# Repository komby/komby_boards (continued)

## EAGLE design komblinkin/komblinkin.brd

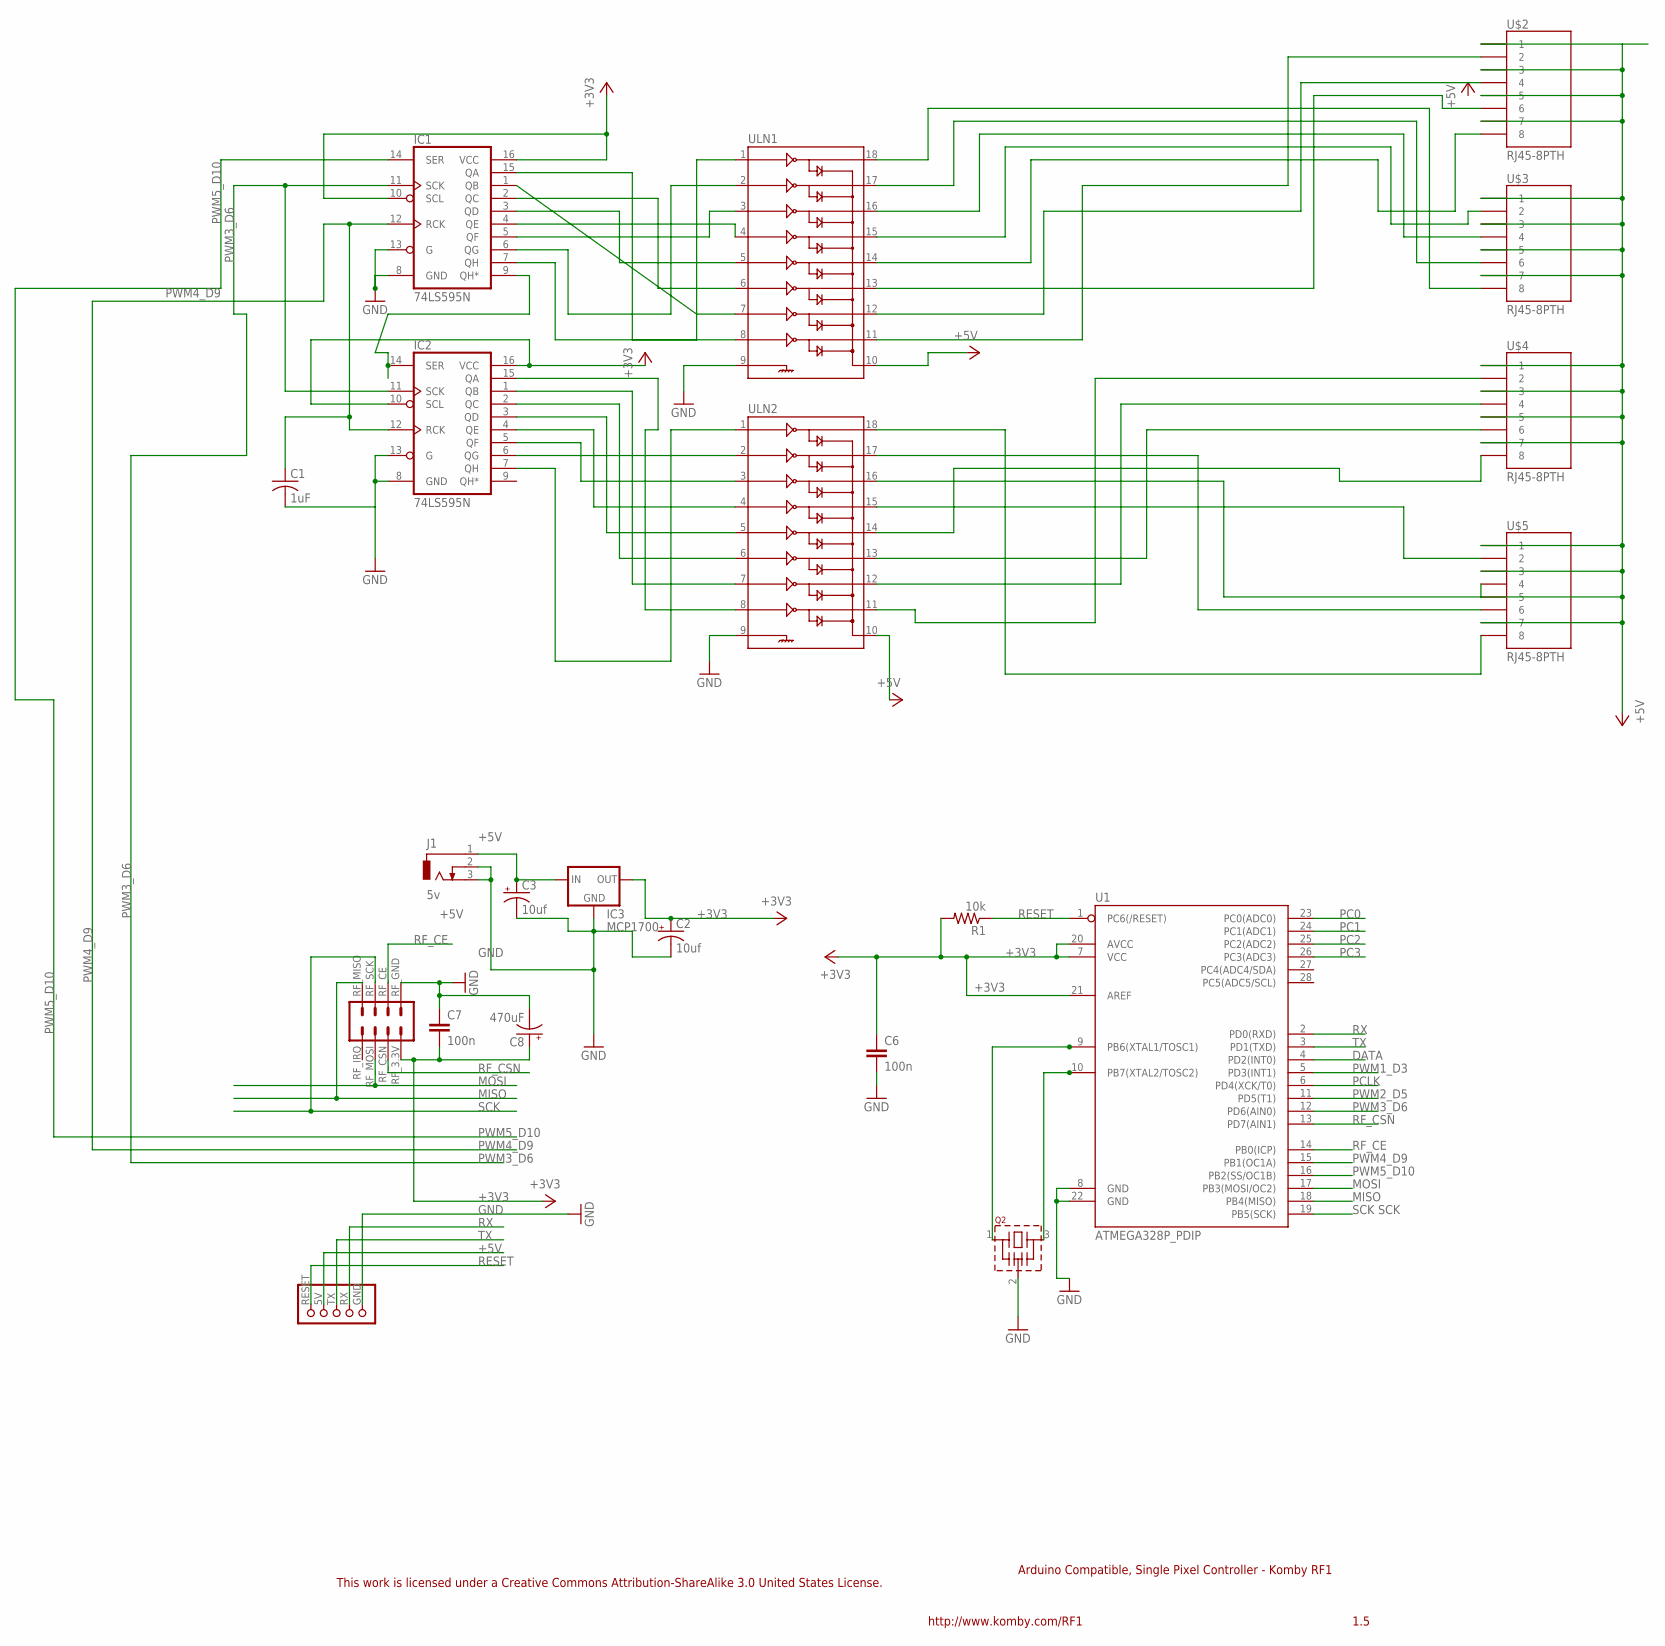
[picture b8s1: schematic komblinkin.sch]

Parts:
C1: 1uF; C050-025X075
C2: 10uf; E1,8-4
C3: 10uf; E5-8,5
C6, C7: 100n; C025-024X044
C8: 470uF; E5-8,5
IC1, IC2: 74LS595N; DIL16
IC3: MCP1700; TO92
J1: 5v; DCJ0303
Q2: CSTLS_X
R1: 10k; 0207/7
U1: ATMEGA328P_PDIP; DIL28-3
U$1: KOMBY_TTL_SERIAL; KOMBY_SERIAL_FOOTPRINT
U$2, U$3, U$4, U$5: RJ45-8PTH; RJ45-8
U$8: NRF24L01_HEADER; NRF24L01
ULN1, ULN2: ULN2803DIP; DIL18

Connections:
+3V3: C2.+, C6.1, C7.2, C8.+, IC1.10 (SCL), IC1.16 (VCC), IC2.10 (SCL), IC2.16 (VCC), IC3.3 (OUT), R1.2, U1.7 (VCC), U1.20 (AVCC), U1.21 (AREF), U$8.RF_3.3V
+5V: C3.+, IC3.2 (IN), J1.1, U$1.5V, U$2.1, U$2.3, U$2.5, U$2.7, U$3.1, U$3.3, U$3.5, U$3.7, U$4.1, U$4.3, U$4.5, U$4.7, U$5.1, U$5.3, U$5.5, U$5.7, ULN1.10, ULN2.10
DATA: U1.4 (PD2(INT0))
GND: C1.2, C2.-, C3.-, C6.2, C7.1, C8.-, IC1.8 (GND), IC1.13 (G), IC2.8 (GND), IC2.13 (G), IC3.1 (GND), J1.2, J1.3, Q2.2 (VSS), U1.8 (GND), U1.22 (GND), U$1.GND, U$8.RF_GND (RFGND_1), ULN1.9, ULN2.9
MISO: U1.18 (PB4(MISO)), U$8.RF_MISO
MOSI: U1.17 (PB3(MOSI/OC2)), U$8.RF_MOSI
unnamed: U$5.8, ULN2.18
unnamed: IC1.15 (QA), ULN1.8
unnamed: IC1.1 (QB), ULN1.7
unnamed: U$3.8, ULN1.18
unnamed: IC1.2 (QC), ULN1.6
unnamed: IC1.3 (QD), ULN1.5
unnamed: IC1.4 (QE), ULN1.4
unnamed: IC1.5 (QF), ULN1.3
unnamed: IC1.9 (QH*), IC2.14 (SER)
unnamed: IC1.6 (QG), ULN1.2
unnamed: U$3.6, ULN1.17
unnamed: IC1.7 (QH), ULN1.1
unnamed: Q2.3, U1.10 (PB7(XTAL2/TOSC2))
unnamed: IC2.1 (QB), ULN2.7
unnamed: IC2.2 (QC), ULN2.6
unnamed: U$3.4, ULN1.16
unnamed: IC2.3 (QD), ULN2.5
unnamed: IC2.4 (QE), ULN2.4
unnamed: IC2.5 (QF), ULN2.3
unnamed: IC2.6 (QG), ULN2.2
unnamed: IC2.7 (QH), ULN2.1
unnamed: U$3.2, ULN1.15
unnamed: U$5.6, ULN2.17
unnamed: U$5.4, ULN2.16
unnamed: U$5.2, ULN2.15
unnamed: U$4.8, ULN2.14
unnamed: U$4.6, ULN2.13
unnamed: U$4.4, ULN2.12
unnamed: U$4.2, ULN2.11
unnamed: IC2.15 (QA), ULN2.8
unnamed: Q2.1, U1.9 (PB6(XTAL1/TOSC1))
unnamed: U$2.8, ULN1.14
unnamed: U$2.6, ULN1.13
unnamed: U$2.4, ULN1.12
unnamed: U$2.2, ULN1.11
PC0: U1.23 (PC0(ADC0))
PC1: U1.24 (PC1(ADC1))
PC2: U1.25 (PC2(ADC2))
PC3: U1.26 (PC3(ADC3))
PCLK: U1.6 (PD4(XCK/T0))
PWM1_D3: U1.5 (PD3(INT1))
PWM2_D5: U1.11 (PD5(T1))
PWM3_D6: IC1.11 (SCK), IC2.11 (SCK), U1.12 (PD6(AIN0))
PWM4_D9: C1.1, IC1.12 (RCK), IC2.12 (RCK), U1.15 (PB1(OC1A))
PWM5_D10: IC1.14 (SER), U1.16 (PB2(SS/OC1B))
RESET: R1.1, U1.1 (PC6(/RESET)), U$1.RESET
RF_CE: U1.14 (PB0(ICP)), U$8.RF_CE
RF_CSN: U1.13 (PD7(AIN1)), U$8.RF_CSN
RX: U1.2 (PD0(RXD)), U$1.RX
SCK: U1.19 (PB5(SCK)), U$8.RF_SCK
TX: U1.3 (PD1(TXD)), U$1.TX

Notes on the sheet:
Arduino Compatible, Single Pixel Controller - Komby RF1
1.5
http://www.komby.com/RF1
This work is licensed under a Creative Commons Attribution-ShareAlike 3.0 United States License.

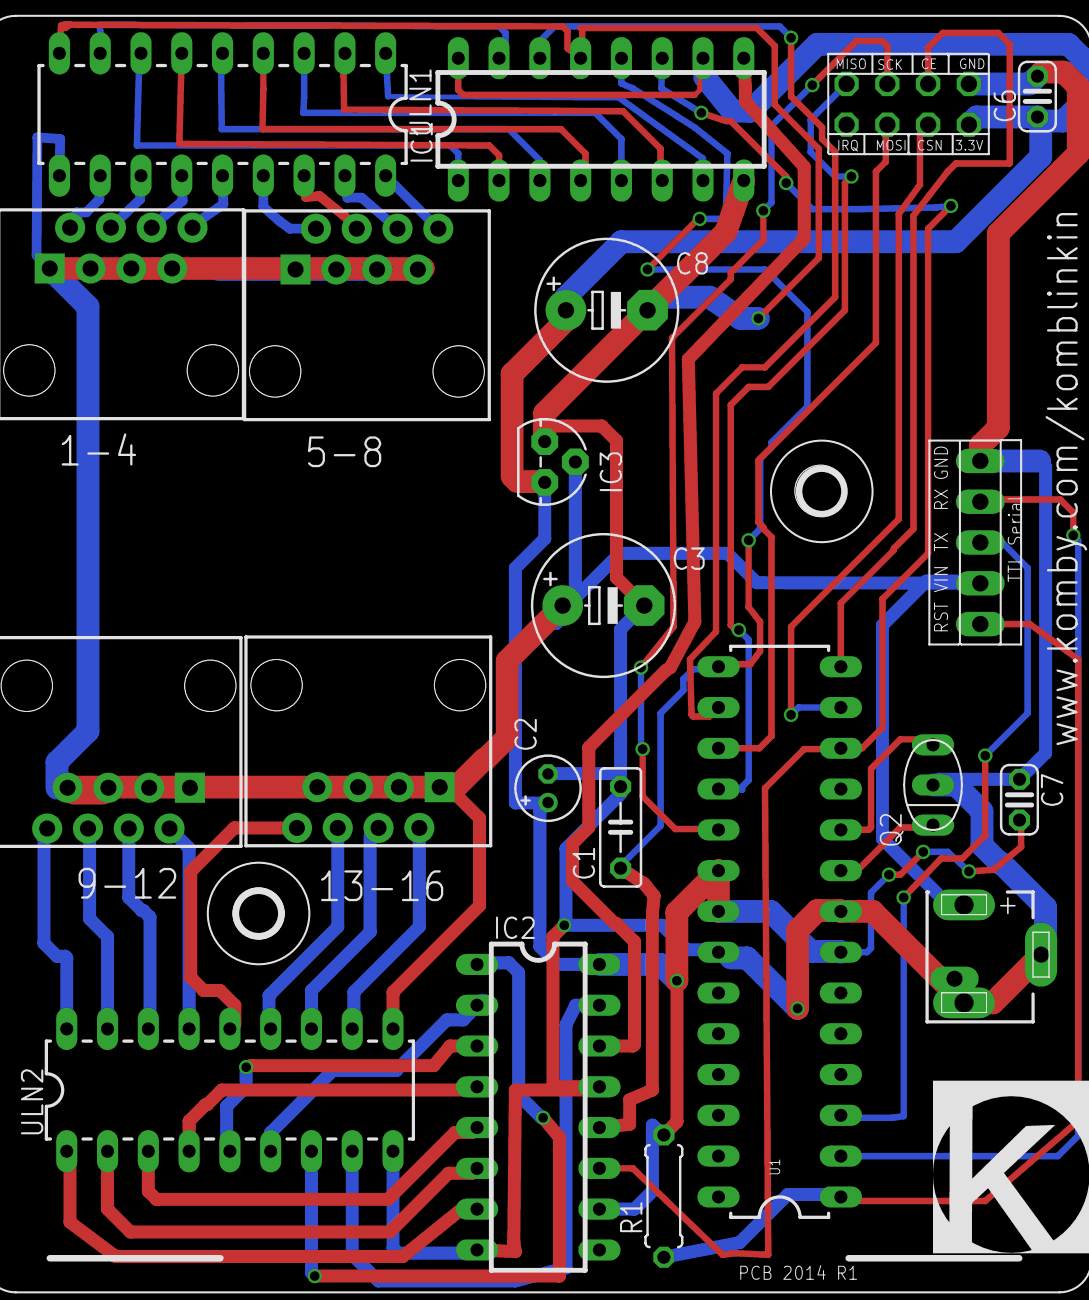
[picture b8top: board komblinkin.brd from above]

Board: 2 copper layers, 23 parts (0 on the bottom side), 49 nets.

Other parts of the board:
U$6: TA200FTPRNT
U$7: KOMBY_LOGO_1CMX1CM

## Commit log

2014-02-08 Initial commit of 2014 version
2014-02-08 2014 versions for FTDI and minimalist
2014-02-08 added serial reset and through hole kombee boards
2014-05-21 added new boards for isp and serial
2014-07-10 Not working version of the RS485 board for croudsourcing help!
    SOS!
2014-08-19 learned to spell, again.
2014-08-19 updated with new revisions
    RF1 RS485 current version, and new Serial board
2015-03-19 Add KombyPiMini board ordered in January of 2015
2015-03-19 Update KombyPiMini with properly oriented nRF
2015-03-19 Add KombyPi mixed board with nRF, pixel output, and RTC.
2015-03-19 Update KombyPi mixed boards to be cleaner layout.
2015-03-19 Update KombyPi to have proper orientation for nRF
2015-03-19 Add dual nRF board initial layout
2015-03-19 Add nRF and RTC board ordered March 2015.
2015-05-05 Move to subdirectory to import into Komby's main repo.
2015-10-21 Create MEGA_shield
2015-10-22 Board files for MEGA Shield
    RF shield for a Arduino MEGA
2016-03-17 Added SSR4 Board Files
    SSR4 Triac expansion board for the RF1
2016-05-15 Added SSR8
    Schmetic, Board, and gerbers for the SSR8. Initial release
